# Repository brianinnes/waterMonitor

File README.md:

# Water Monitor

ESP32 project to monitor water quality.

This project uses an ESP32 DevKitC device along with a flow meter and 2 TDS meter components to measure water usage and monitor efficiency of a water filter.

Documentation can be found [here : https://brianinnes.github.io/waterMonitor/](https://brianinnes.github.io/waterMonitor/)

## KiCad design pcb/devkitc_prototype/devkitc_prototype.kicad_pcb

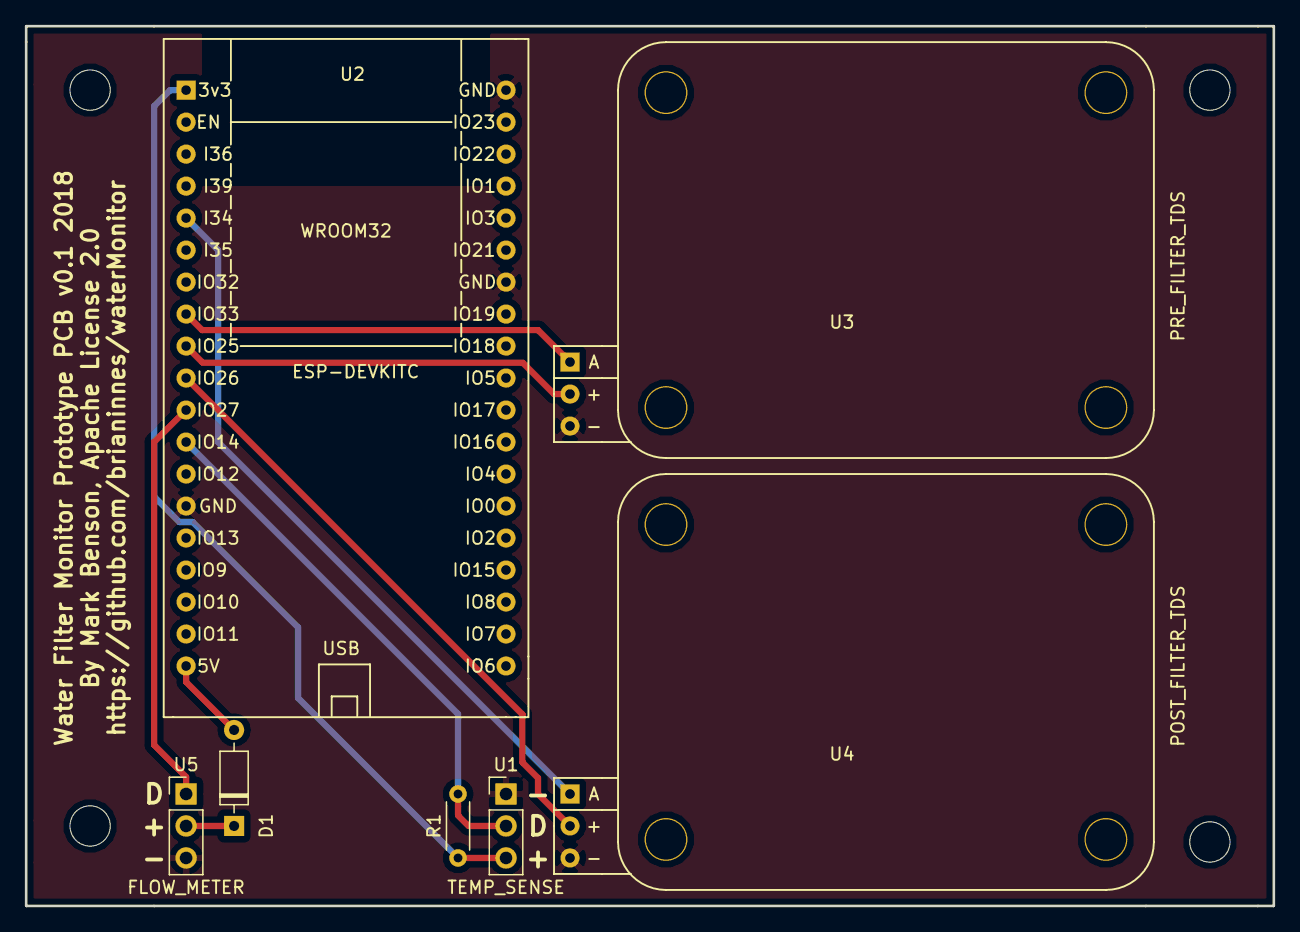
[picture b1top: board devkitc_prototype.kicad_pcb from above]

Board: 2 copper layers, 99.1 x 69.8 mm, 7 parts (0 on the bottom side), 10 nets.

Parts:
D1: 1N418; D_DO-35_SOD27_P7.62mm_Horizontal
R1: 4.7k; R_Axial_DIN0204_L3.6mm_D1.6mm_P5.08mm_Horizontal
U1: TEMP_SENSE; PinHeader_1x03_P2.54mm_Vertical
U2: ESP-DEVKITC; DEVKITC
U3: PRE_FILTER_TDS; DFRobot_Gravity_TDS_Sensor
U4: POST_FILTER_TDS; DFRobot_Gravity_TDS_Sensor
U5: FLOW_METER; PinHeader_1x03_P2.54mm_Vertical

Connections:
/3v3: R1.1, U1.3, U2.1
/5v: D1.2, U2.19
/FLOW_OUT: U2.11, U5.1
/OW_BUS: R1.2, U1.2, U2.12
/TDS_POST_OUT: U2.5, U4.1
/TDS_POST_PWR: U2.10, U4.2
/TDS_PRE_OUT: U2.8, U3.1
/TDS_PRE_PWR: U2.9, U3.2
GND: U1.1, U2.14, U2.32, U2.38, U3.3, U4.3, U5.3
unnamed: D1.1, U5.2

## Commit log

2018-10-18 Initial flow meter content
2018-10-18 added project config to .gitignore to prevent password being committed
2018-10-19 Added vagrant test backend
2018-10-25 host AP and captive portal initial implementation with modified httpd
2018-11-01 fixed vagrant for Windows host
2018-11-01 Updated instructions for Vagrant setup
2018-11-01 updated gitignore
2018-11-01 fix .gitignore
2018-11-04 renamed http_server component inline with edp-idf component
2018-11-04 updated README for setup instructions
2018-11-11 updated to overcome upgrade manual intervention recently released
2018-11-27 Implement water quality tasks
2018-11-27 Converted mutex to binary semaphore to avoid error
2018-11-27 Added persistence
2018-11-27 reduced persistence delay
2018-11-27 Added water quality to Node-RED dashboard
2018-11-28 Update issue templates
2018-11-28 Set theme jekyll-theme-midnight
2018-11-28 added docs folder
2018-11-28 Added basic doc placeholders
2018-11-28 renamed compiling doc
2018-11-28 moved docs config file
2018-11-28 Updated README to point to project docs
2018-11-28 improved error handling
2018-11-28 fix semaphore take return code handling
2018-11-28 pulses to litres fix
2018-11-29 Improved reconnection when MQTT disconnects
2018-12-09 Removed the http_server component as this has been updated - breaks captive portal
2018-12-09 Add temperature sensor and TDS calculations
2018-12-09 Updated Node-RED flow
2018-12-09 Updated wiring documentation
2018-12-09 Added mDNS resolution to device
2018-12-11 Prototype PCB
    Prototype PCB to testing the electronics.
2018-12-11 Force add pcb lib file
    Manually added pcb .lib file that was excluded because of .gitignore
2019-02-26 fix persist pulses
2019-02-26 add Web Filesystem
2019-02-26 initial config web content
2019-02-26 update cert config
2019-02-26 remove captive portal code
2019-02-26 updated .gotignore file
2019-06-07 additional components for thermometer
2019-06-27 updated main
2019-06-27 updated vagrant file
2019-06-27 updated defs in header
2019-06-27 Config

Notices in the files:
pcb/devkitc_prototype/devkitc_prototype.kicad_pcb:
Licence: MIT
By Mark Benson, Apache License 2.0
